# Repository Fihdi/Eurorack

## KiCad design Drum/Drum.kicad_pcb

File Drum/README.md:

Simple Kick-Drum module with triangle core VCO with variable waveshape (morphs between triangle and square wave), VCA and Envelope Generator. The envelope has CV control over the accent (maximum peak of the envelope) and decay.

The VCA is a discrete differential amplifier with an opamp amplifier stage on the output.

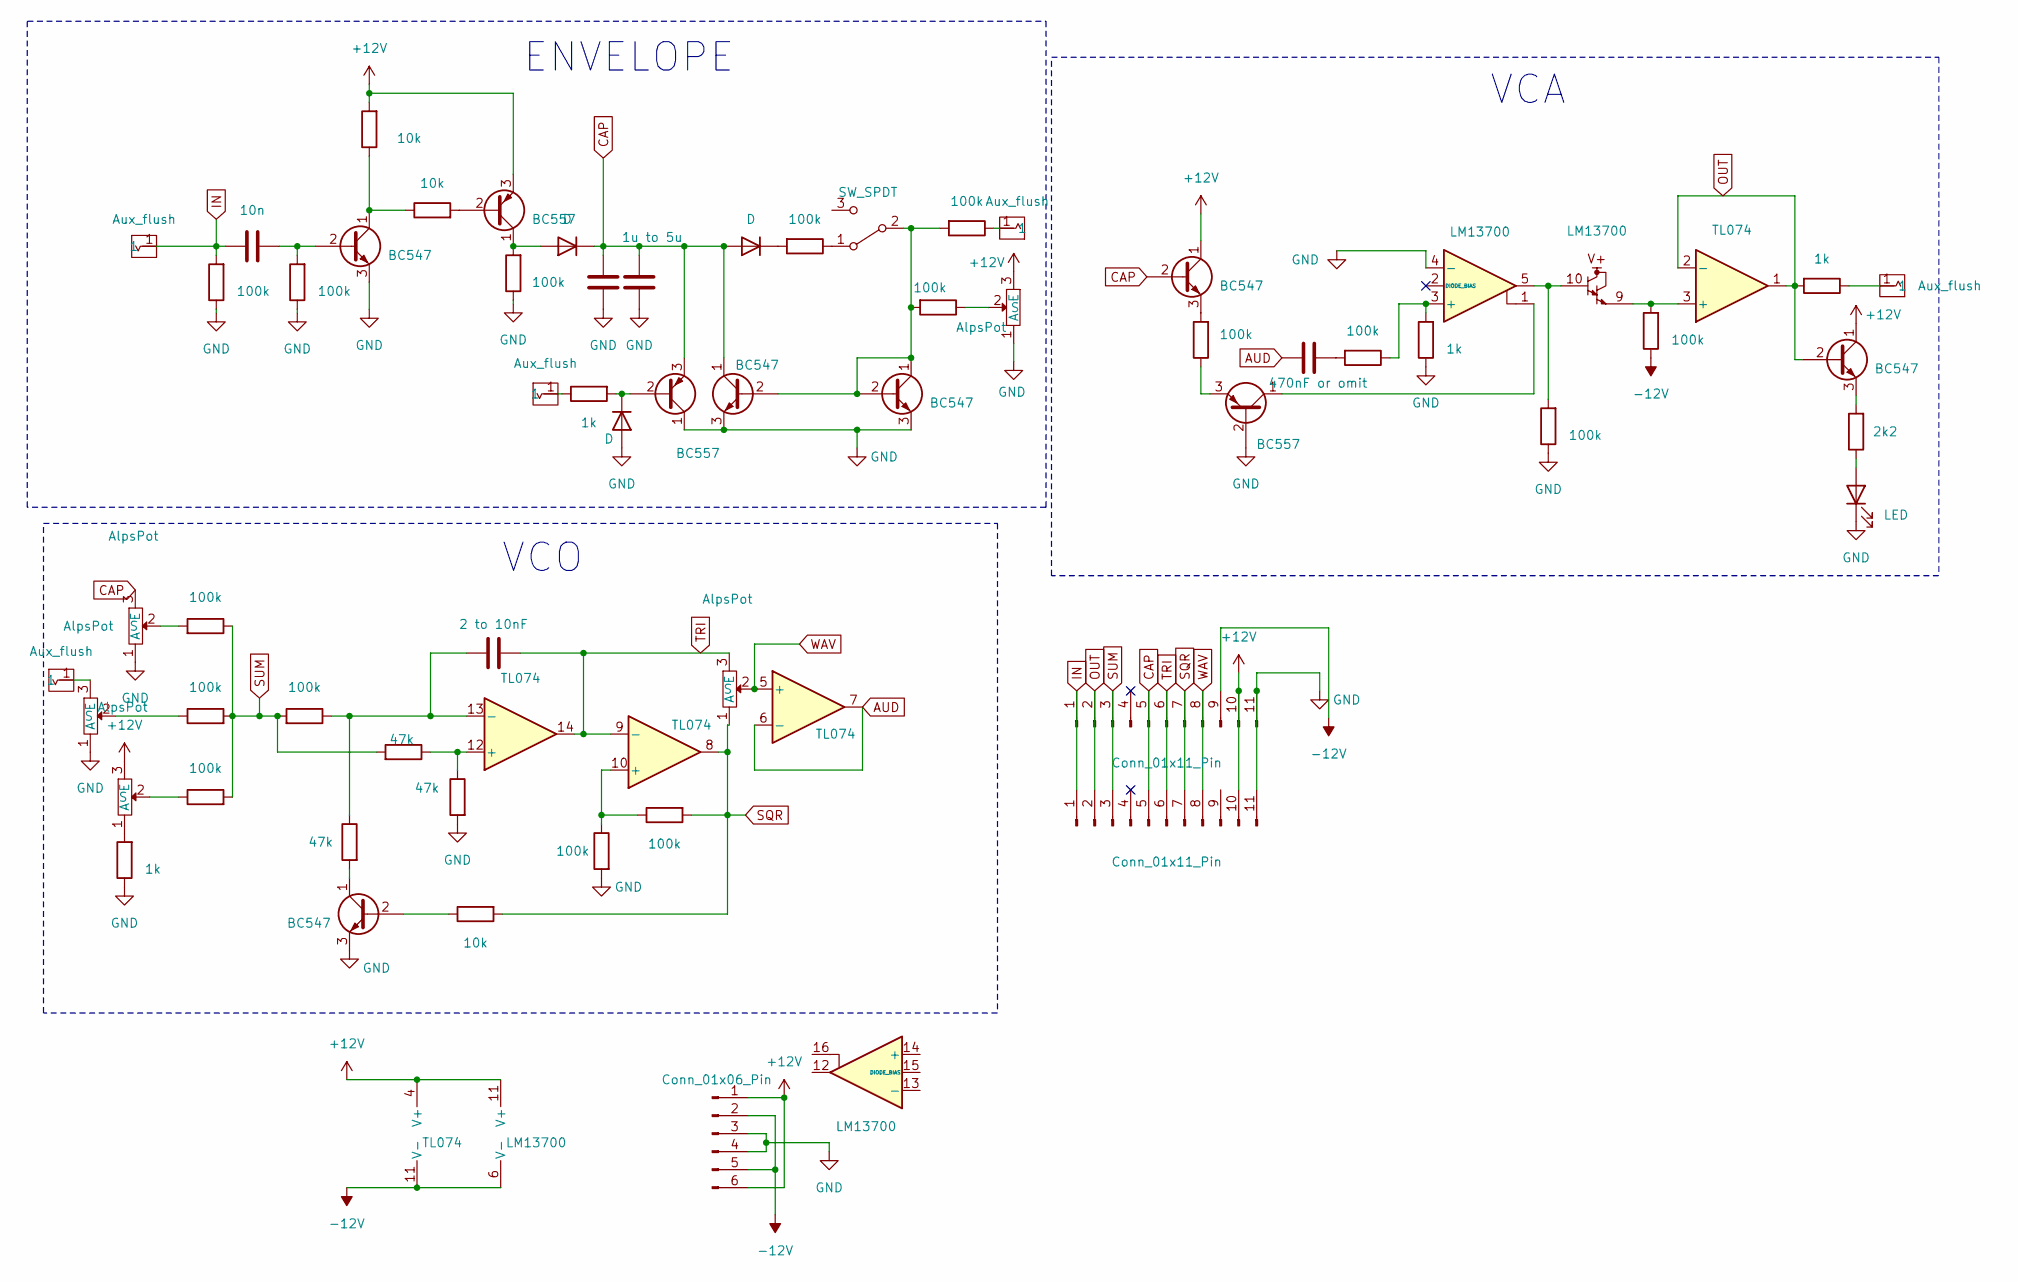
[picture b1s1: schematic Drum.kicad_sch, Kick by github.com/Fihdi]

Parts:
C1: 10n; C_Axial_L5.1mm_D3.1mm_P7.50mm_Horizontal
C2: 1u to 5u; C_Axial_L5.1mm_D3.1mm_P7.50mm_Horizontal
C3: 470nF or omit; C_Axial_L5.1mm_D3.1mm_P7.50mm_Horizontal
C4: 2 to 10nF; C_Axial_L5.1mm_D3.1mm_P7.50mm_Horizontal
C7: 5n; C_Axial_L5.1mm_D3.1mm_P7.50mm_Horizontal
D1, D3, D4: D; D_A-405_P7.62mm_Horizontal
D2: LED; LED_D5.0mm
J1: Conn_01x06_Pin; PinHeader_1x06_P2.54mm_Vertical
J2, J3: Conn_01x11_Pin; PinHeader_1x11_P2.54mm_Vertical
Q2, Q3, Q6, Q7, Q8, Q9: BC547; TO-92L_Inline_Wide
Q4, Q5, Q10: BC557; TO-92L_Inline_Wide
R1, R5, R9, R12, R13: AlpsPot
R2, R3, R4, R6, R7, R8, R10, R11, R14, R18, R19, R20, R21, R24, R29, R30: 100k; R_Axial_DIN0207_L6.3mm_D2.5mm_P7.62mm_Horizontal
R15, R28, R31: 47k; R_Axial_DIN0207_L6.3mm_D2.5mm_P7.62mm_Horizontal
R16, R25, R27, R33: 1k; R_Axial_DIN0207_L6.3mm_D2.5mm_P7.62mm_Horizontal
R17: 2k2; R_Axial_DIN0207_L6.3mm_D2.5mm_P7.62mm_Horizontal
R22, R23, R32: 10k; R_Axial_DIN0207_L6.3mm_D2.5mm_P7.62mm_Horizontal
SW1: SW_SPDT; Switch
U1, U2, U6, U7, U8: Aux_flush; 3mm5 Mono Aux
U3: TL074; DIP-14_W7.62mm
U5: LM13700; DIP-16_W7.62mm

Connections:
+12V: J1.1, J1.6, J2.10, J3.10, Q3.1 (C), Q4.3 (E), Q7.1 (C), R1.3 (E), R5.3 (E), R22.2, U3.4 (V+), U5.11 (V+)
-12V: J1.2, J1.5, J3.9, R18.1, U3.11 (V-), U5.6 (V-)
AUD: C3.1, U3.6 (-), U3.7
CAP: C2.2, C7.2, D1.1 (K), D3.2 (A), J2.5, J3.5, Q3.2 (B), Q8.1 (C), Q10.3 (E), R9.3 (E)
GND: C2.1, C7.1, D2.1 (K), D4.2 (A), J1.3, J1.4, J2.11, J3.11, Q2.3 (E), Q5.2 (B), Q6.3 (E), Q8.3 (E), Q9.3 (E), Q10.1 (C), R2.1, R4.1, R5.1 (A), R6.1, R8.1, R9.1 (A), R13.1 (A), R16.1, R25.1, R28.2, R30.2, U5.4 (-)
IN: C1.1, J2.1, J3.1, R8.2, U2.1
unnamed: C3.2, R7.2
unnamed: D1.2 (A), Q4.1 (C), R6.2
unnamed: D2.2 (A), R17.1
unnamed: D3.1 (K), R20.2
unnamed: D4.1 (K), Q10.2 (B), R33.2
unnamed: C1.2, Q2.2 (B), R4.2
unnamed: Q2.1 (C), R22.1, R23.1
unnamed: Q3.3 (E), R24.2
unnamed: Q4.2 (B), R23.2
unnamed: Q5.1 (C), U5.1
unnamed: Q5.3 (E), R24.1
unnamed: Q6.2 (B), R32.1
unnamed: Q6.1 (C), R31.2
unnamed: Q7.3 (E), R17.2
unnamed: Q8.2 (B), Q9.1 (C), Q9.2 (B), R10.2, R19.2, SW1.2 (B)
unnamed: R1.1 (A), R16.2
unnamed: R1.2 (S), R3.1
unnamed: R2.2, U5.5, U5.10
unnamed: R5.2 (S), R10.1
unnamed: R9.2 (S), R21.2
unnamed: R13.3 (E), U1.1
unnamed: R13.2 (S), R14.1
unnamed: R19.1, U8.1
unnamed: R27.1, U6.1
unnamed: R33.1, U7.1
unnamed: R20.1, SW1.1 (A)
unnamed: R18.2, U3.3 (+), U5.9
unnamed: R29.1, R30.1, U3.10 (+)
unnamed: R15.1, R28.1, U3.12 (+)
unnamed: C4.2, R11.1, R31.1, U3.13 (-)
unnamed: R7.1, R25.2, U5.3 (+)
OUT: J2.2, J3.2, Q7.2 (B), R27.2, U3.1, U3.2 (-)
SQR: J2.7, J3.7, R12.1 (A), R29.2, R32.2, U3.8
SUM: J2.3, J3.3, R3.2, R11.2, R14.2, R15.2, R21.1
TRI: C4.1, J2.6, J3.6, R12.3 (E), U3.9 (-), U3.14
WAV: J2.8, J3.8, R12.2 (S), U3.5 (+)

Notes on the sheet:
VCA
ENVELOPE
VCO

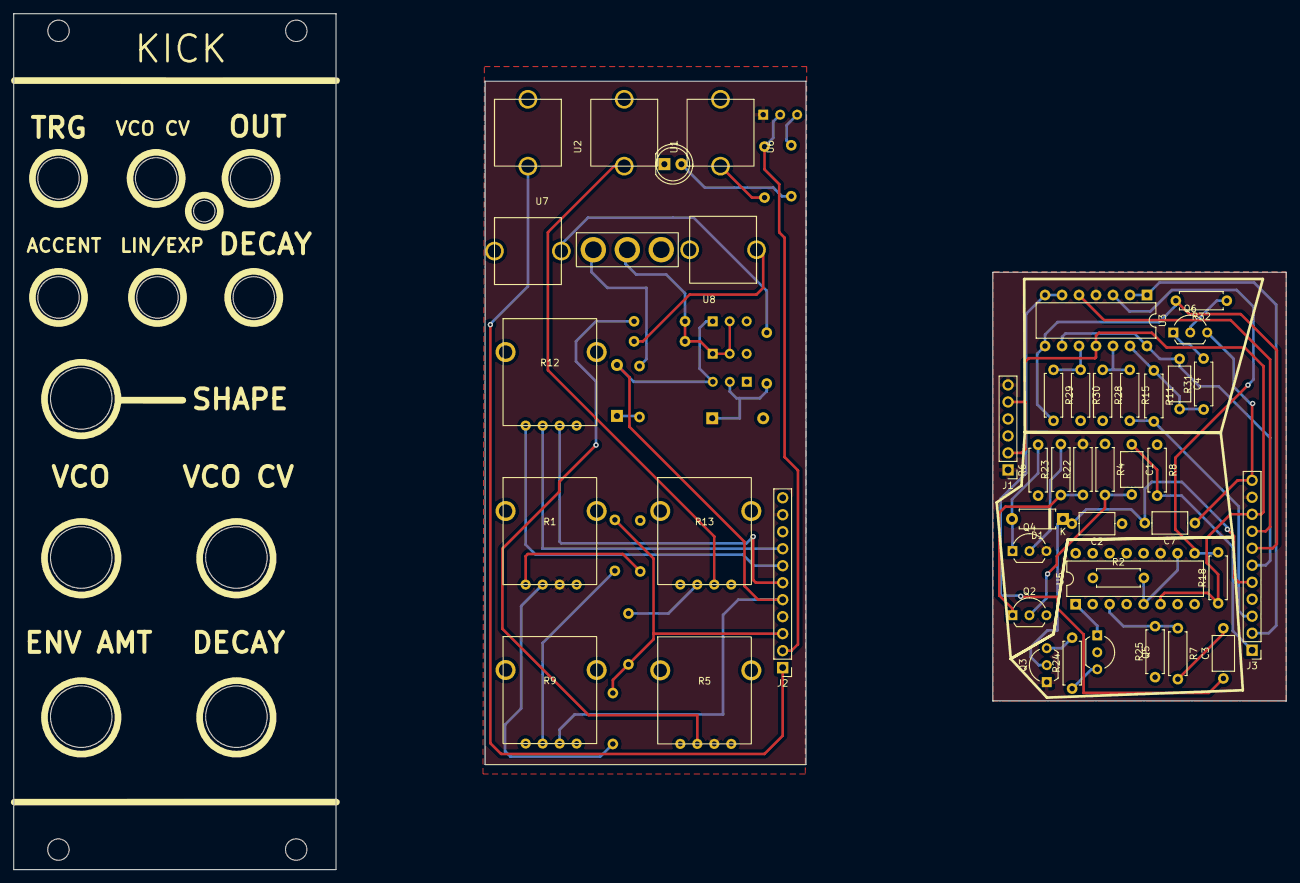
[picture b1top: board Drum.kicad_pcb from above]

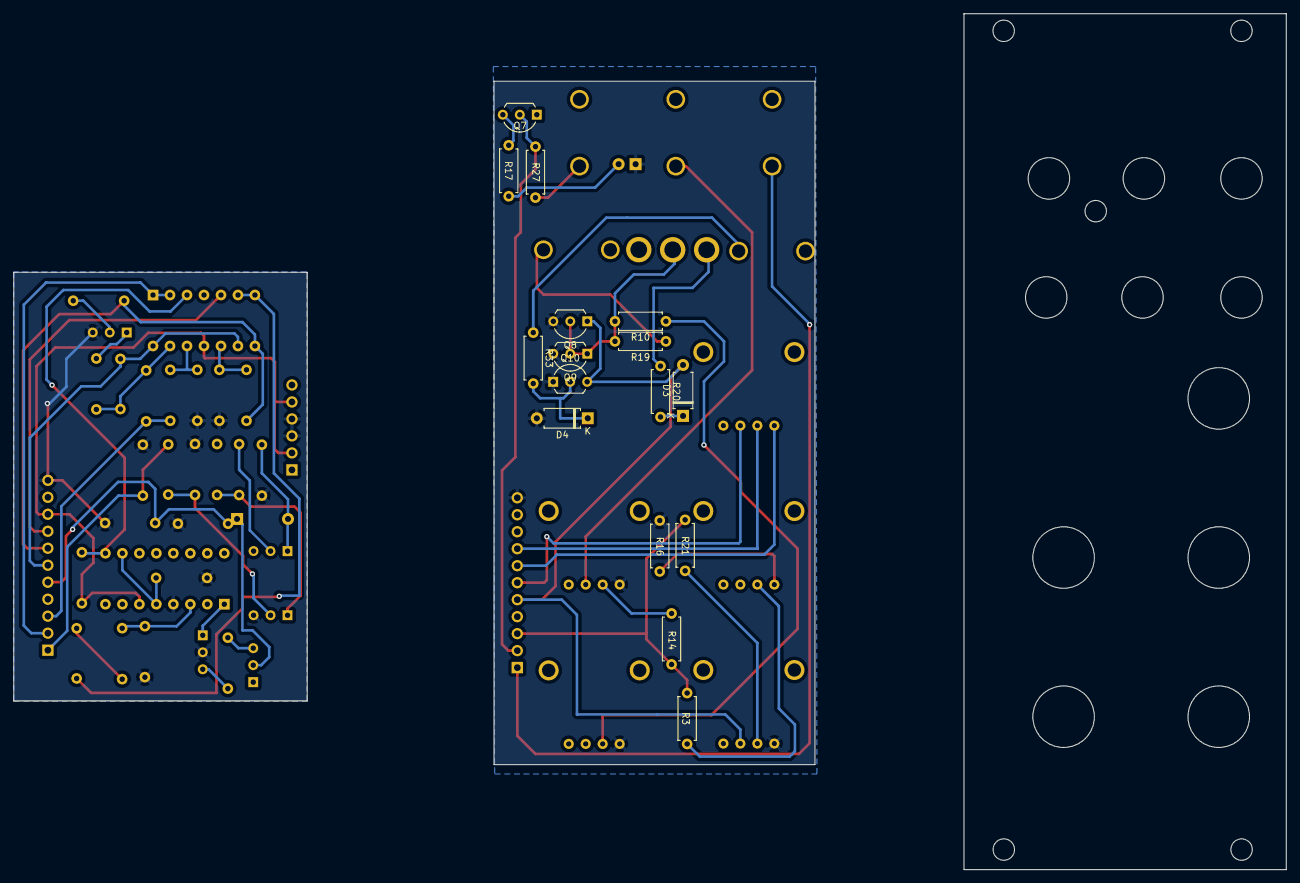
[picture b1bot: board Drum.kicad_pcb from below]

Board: 2 copper layers, 190.3 x 128.0 mm, 61 parts (16 on the bottom side), 42 nets.

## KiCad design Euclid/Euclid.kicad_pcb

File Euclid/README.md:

2 Channel Euclidean Rhythm Generator.

Has an internal clock generator which can be used as a master clock. This clock will be overwritten if an external signal on CLK IN is detected. If no signal is detected at CLK IN, the internal clock is used again. 

Channel parameters such as length and steps can be changed via pots and shifted via the SHIFT input.

A rising edge at RESET resets the channels assignments.

Upload the file "Bernoulli-Gates.ino" to repurpose the module as a "coin toss" module similar to Mutable Instruments Branches. Send a Gate or Trigger into the CLK IN input and the signal will be routed to either OUT1 or OUT2 depending on a probability. The probability is set by the rate knob.

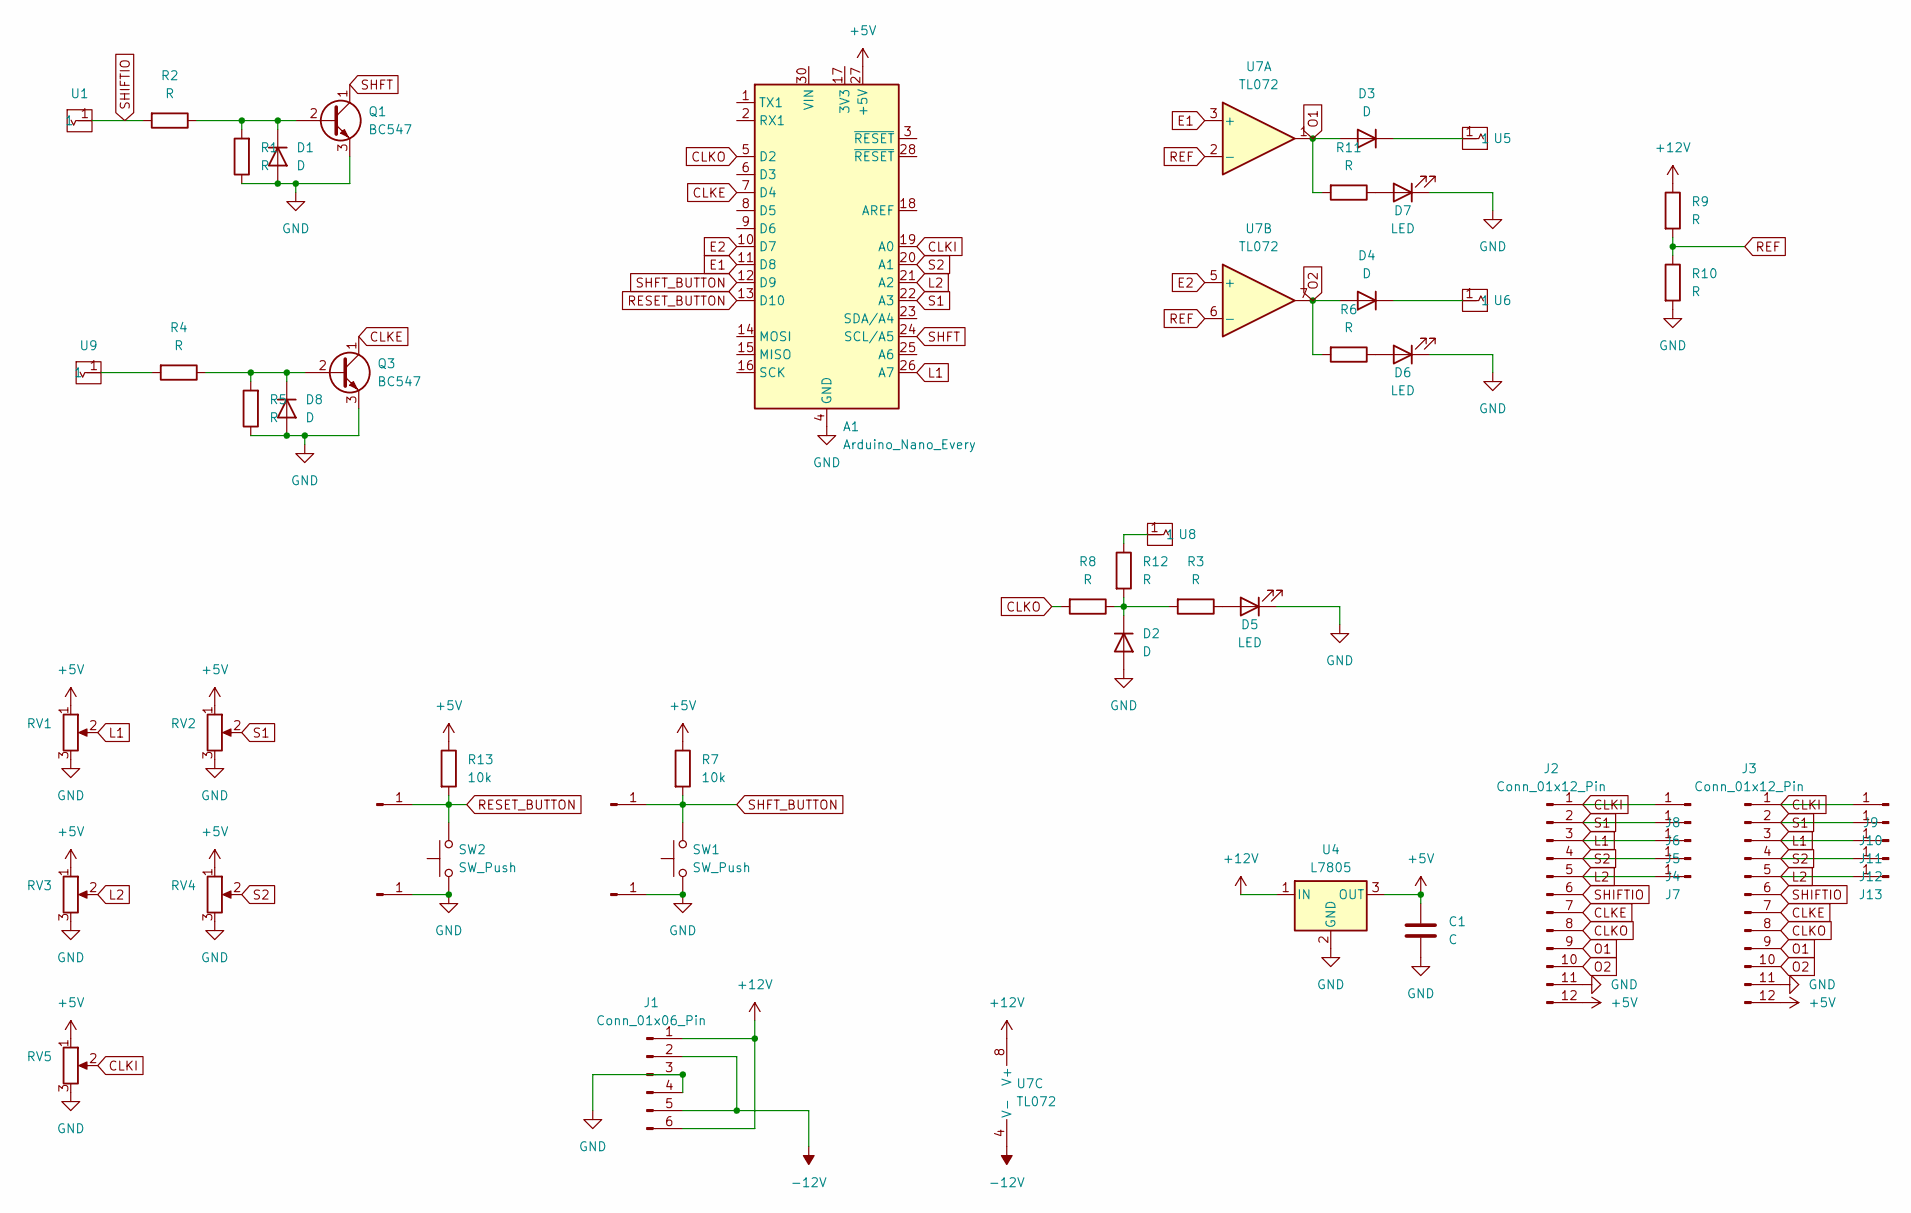
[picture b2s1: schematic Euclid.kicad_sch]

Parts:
A1: Arduino_Nano_Every; Arduino_Nano
C1: C; C_Rect_L10.3mm_W4.5mm_P7.50mm_MKS4
D1, D2, D3, D4, D8: D; D_A-405_P7.62mm_Horizontal
D5, D6, D7: LED; LED_D3.0mm
J1: Conn_01x06_Pin; PinSocket_1x06_P2.54mm_Vertical
J2, J3: Conn_01x12_Pin; PinSocket_1x12_P2.54mm_Vertical
J4, J5, J6, J7, J8, J9, J10, J11, J12, J13, J14, J15, J16, J17: Conn_01x01_Pin; PinSocket_1x01_P2.54mm_Vertical
Q1, Q3: BC547; TO-92_Inline_Wide
R1, R2, R3, R4, R5, R6, R8, R9, R10, R11, R12: R; R_Axial_DIN0207_L6.3mm_D2.5mm_P7.62mm_Horizontal
R7, R13: 10k; R_Axial_DIN0207_L6.3mm_D2.5mm_P7.62mm_Horizontal
RV1, RV2, RV3, RV4, RV5: R_Potentiometer; AlpsPot
SW1, SW2: SW_Push
U1, U5, U6, U8, U9: Aux_flush; 3mm5 Mono Aux
U4: L7805; TO-252-3_TabPin2
U7: TL072; DIP-8_W7.62mm

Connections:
+5V: A1.27 (+5V), C1.1, J2.12, J3.12, R7.1, R13.1, RV1.1, RV2.1, RV3.1, RV4.1, RV5.1, U4.3 (OUT)
+12V: J1.1, J1.6, R9.1, U4.1 (IN), U7.8 (V+)
-12V: J1.2, J1.5, U7.4 (V-)
CLKE: A1.7 (D4), J2.7, J3.7, Q3.1 (C)
CLKI: A1.19 (A0), J2.1, J3.1, J8.1, J9.1, RV5.2
CLKO: A1.5 (D2), J2.8, J3.8, R8.2
E1: A1.11 (D8), U7.3 (+)
E2: A1.10 (D7), U7.5 (+)
GND: A1.4 (GND), A1.29 (GND), C1.2, D1.2 (A), D2.2 (A), D5.1 (K), D6.1 (K), D7.1 (K), D8.2 (A), J1.3, J1.4, J2.11, J3.11, J15.1, J17.1, Q1.3 (E), Q3.3 (E), R1.1, R5.1, R10.2, RV1.3, RV2.3, RV3.3, RV4.3, RV5.3, SW1.1, SW2.1, U4.2 (GND)
L1: A1.26 (A7), J2.3, J3.3, J5.1, J11.1, RV1.2
L2: A1.21 (A2), J2.5, J3.5, J7.1, J13.1, RV3.2
unnamed: D1.1 (K), Q1.2 (B), R1.2, R2.1
unnamed: D2.1 (K), R3.2, R8.1, R12.2
unnamed: D3.1 (K), U5.1
unnamed: D4.1 (K), U6.1
unnamed: D5.2 (A), R3.1
unnamed: D6.2 (A), R6.1
unnamed: D7.2 (A), R11.1
unnamed: D8.1 (K), Q3.2 (B), R4.1, R5.2
unnamed: R4.2, U9.1
unnamed: R12.1, U8.1
O1: D3.2 (A), J2.9, J3.9, R11.2, U7.1
O2: D4.2 (A), J2.10, J3.10, R6.2, U7.7
REF: R9.2, R10.1, U7.2 (-), U7.6 (-)
RESET_BUTTON: A1.13 (D10), J16.1, R13.2, SW2.2
S1: A1.22 (A3), J2.2, J3.2, J6.1, J10.1, RV2.2
S2: A1.20 (A1), J2.4, J3.4, J4.1, J12.1, RV4.2
SHFT: A1.24 (SCL/A5), Q1.1 (C)
SHFT_BUTTON: A1.12 (D9), J14.1, R7.2, SW1.2
SHIFTIO: J2.6, J3.6, R2.2, U1.1

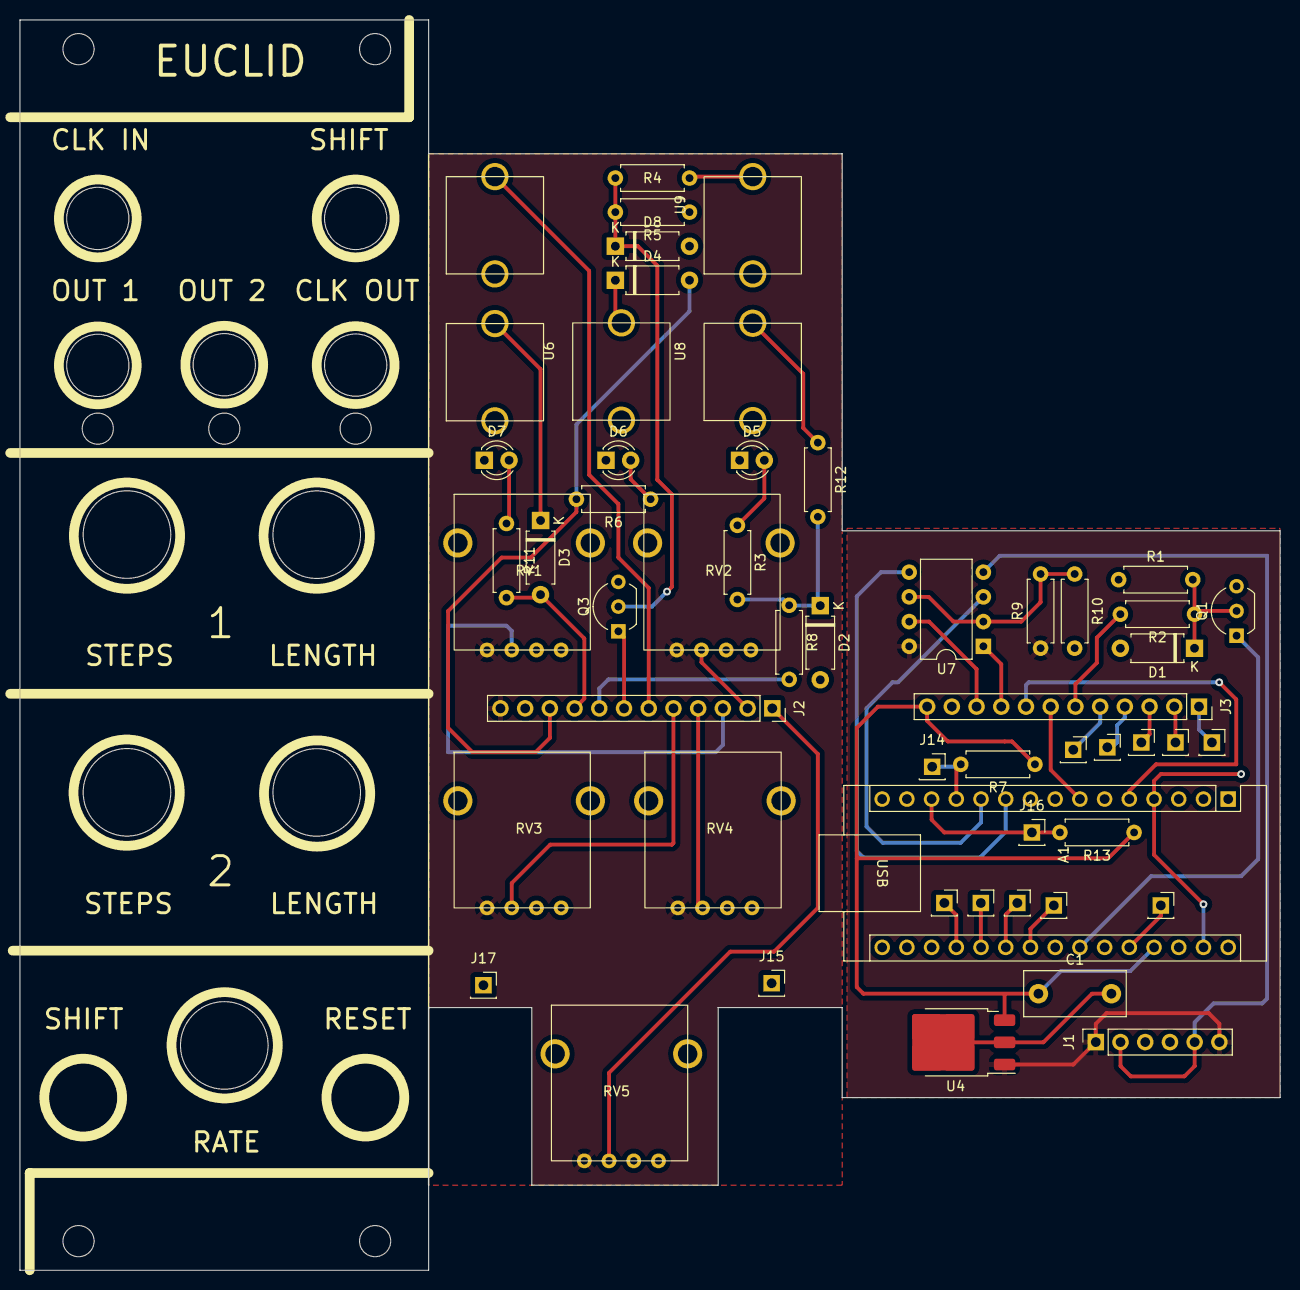
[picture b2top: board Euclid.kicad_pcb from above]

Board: 2 copper layers, 129.5 x 128.5 mm, 54 parts (0 on the bottom side), 30 nets.

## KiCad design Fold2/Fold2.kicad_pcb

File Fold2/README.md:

# A wavefolder with CV control over the amount of folds.

Me and [Davey Graham](https://github.com/DaveyGraham/Daveys_Deadband) were working on wavefolders at the same time independently. A few days after I posted this schematic for a simple wavefolder, Davey has extended upon it:

CAP is the input signal being clamped at +CV and -CV. I then subtract the original signal from the clamped signal to get a folded output.

Extending the clamping circuit with multiple limits and using the same principle as in Buchlas "Timbre Modulation" circuit where the input signal is split into multiple "deadbands" and then re-added and subtracted from each other to produce the folded output, we get the full circuit that was made by Davey Graham. 

The deadbands are made using this diode structure, it can also be seen as a clamping circuit with variable clamping voltages:

An example with the upper limit being 5V and the lower limit being 3V. The output of this circuit follows the input signal as long as it is within the upper and lower limits. The output never exceeds these limits (ignoring the diode drop).

The resistor chain and buffers are there to provide the upper and lower limits for the diodes.

# How to get a folded output from deadbands?

As in the Buchla circuit, every other band is summed together, resulting in two signals A and B (I did not draw the summing stages for simplicity) 
With no input, the bias voltages between the diodes sum up to zero volts, so with 0V in you get 0V out. OK. Boring.

With a sine input the signals A and B cross each other, and when B is subtracted from A, the resulting wave changes in polarity at every crossing, and we get folding. 

# How to add voltage control?

To get a fold, the input voltage needs to cross either the upper or lower limit of the clamping circuit, so the amount of folds depends on the amplitude and how many limits it is crossing. Using a VCA with a high gain gives control over the amplitude and thus the amount of folds. The output of the VCA is also directly fed to the "VCA" output, since you can never have enough VCAs.

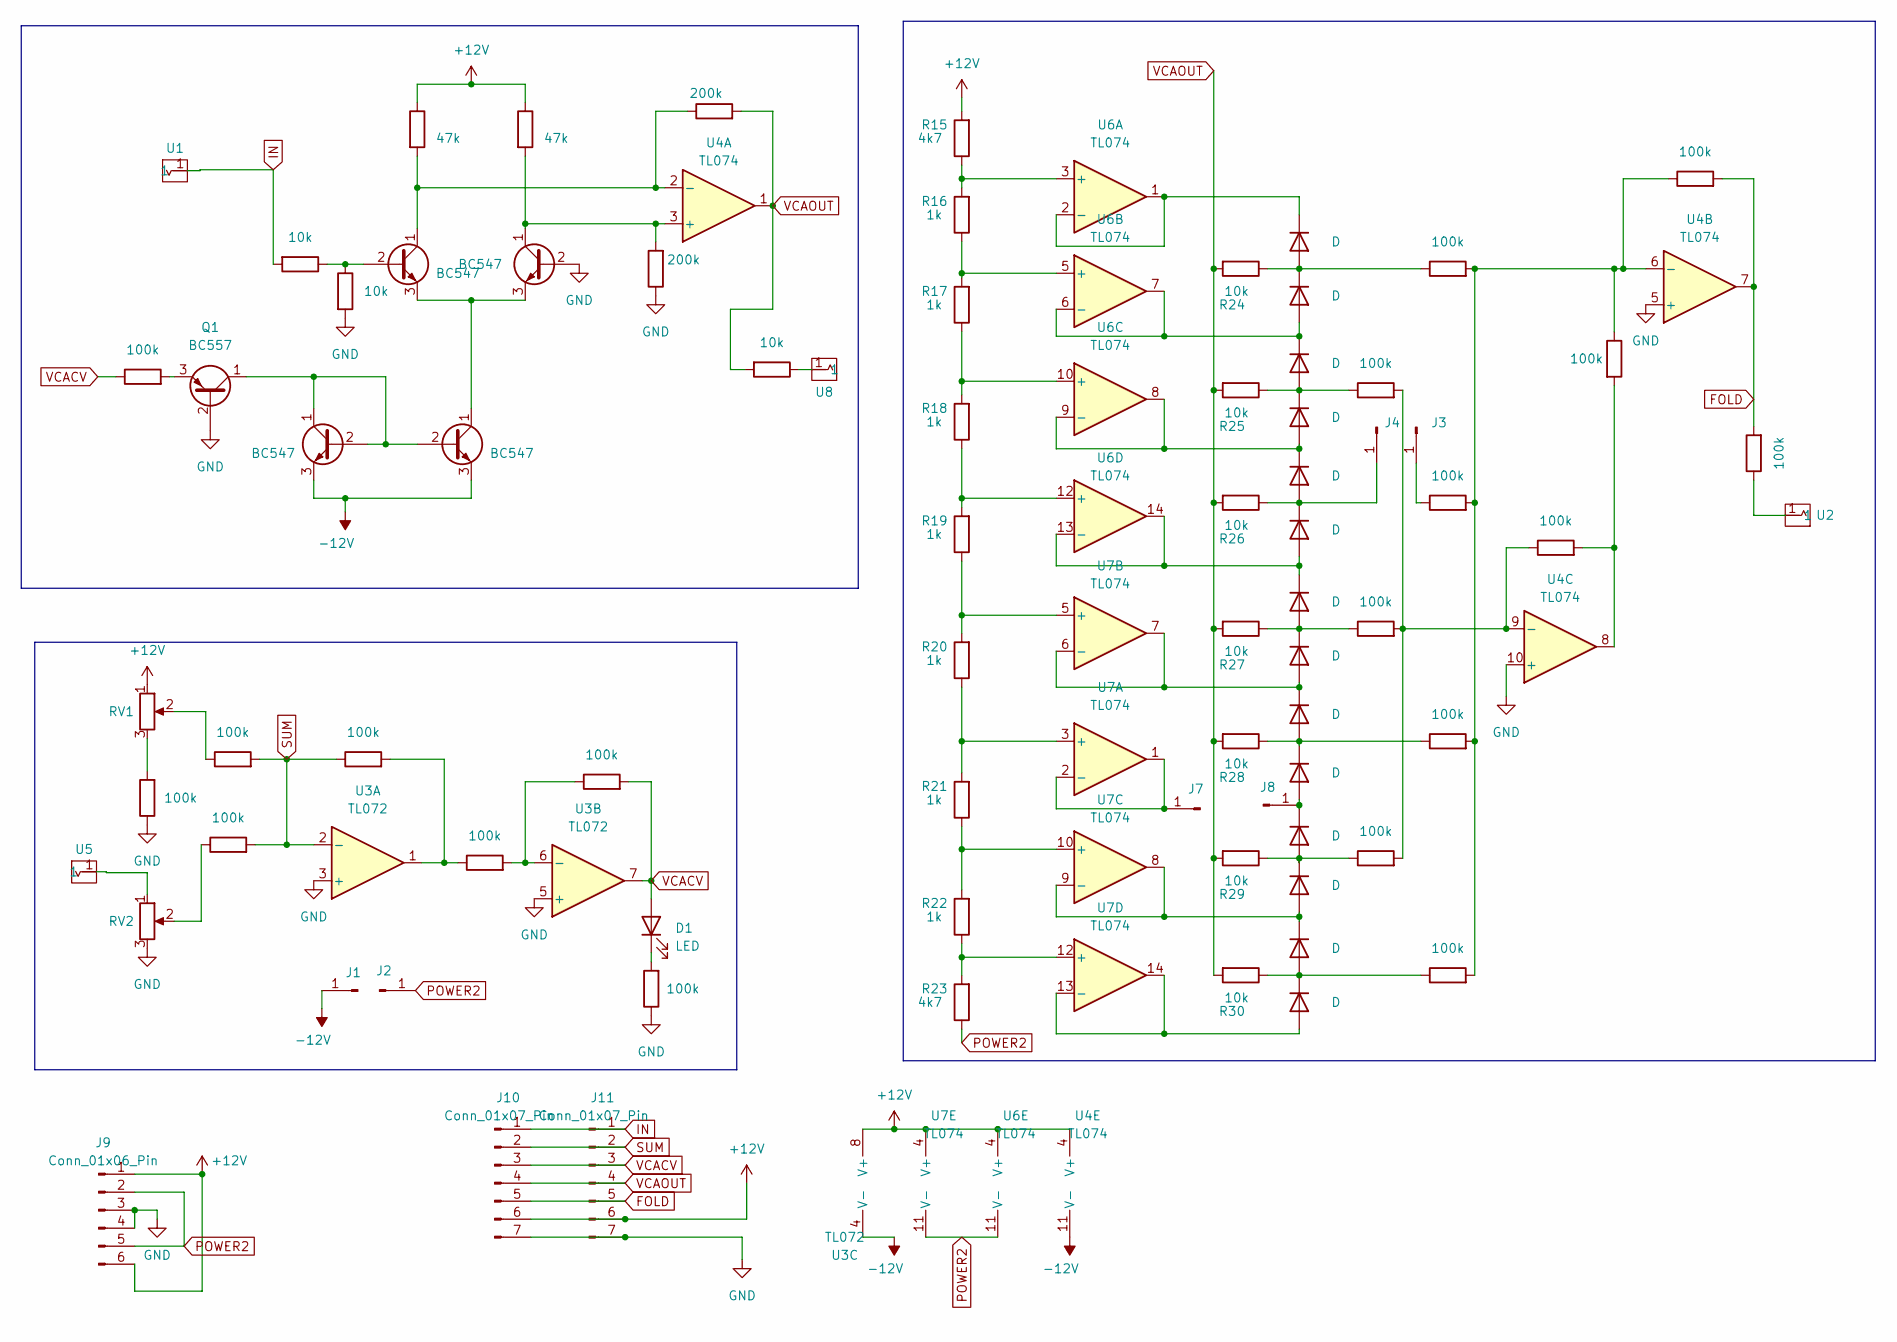
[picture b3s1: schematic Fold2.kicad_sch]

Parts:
D1: LED; LED_D3.0mm
D2, D3, D4, D5, D6, D7, D8, D9, D10, D11, D12, D13, D14, D15: D; D_A-405_P5.08mm_Vertical_AnodeUp
J1, J2, J3, J4, J7, J8: Conn_01x01_Pin; PinSocket_1x01_P2.54mm_Vertical
J9: Conn_01x06_Pin; PinHeader_1x06_P2.54mm_Vertical
J10, J11: Conn_01x07_Pin; PinSocket_1x07_P2.54mm_Vertical
Q1: BC557; TO-92L_Inline_Wide
Q2, Q3, Q4, Q5: BC547; TO-92_Inline_Wide
R1, R2, R3, R6, R8, R10, R11, R14, R31, R32, R33, R34, R35, R36, R37, R38, R39, R40, R42: 100k; R_Axial_DIN0204_L3.6mm_D1.6mm_P7.62mm_Horizontal
R4, R5, R24, R25, R26, R27, R28, R29, R30, R41: 10k; R_Axial_DIN0204_L3.6mm_D1.6mm_P7.62mm_Horizontal
R7, R9: 47k; R_Axial_DIN0204_L3.6mm_D1.6mm_P7.62mm_Horizontal
R12, R13: 200k; R_Axial_DIN0204_L3.6mm_D1.6mm_P7.62mm_Horizontal
R15, R23: 4k7; R_Axial_DIN0204_L3.6mm_D1.6mm_P7.62mm_Horizontal
R16, R17, R18, R19, R20, R21, R22: 1k; R_Axial_DIN0204_L3.6mm_D1.6mm_P7.62mm_Horizontal
RV1, RV2: R_Potentiometer; AlpsPot
U1, U2, U5, U8: Aux_flush; 3mm5 Mono Aux
U3: TL072; DIP-8_W7.62mm
U4, U6, U7: TL074; DIP-14_W7.62mm

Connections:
+12V: J9.1, J9.6, J10.6, J11.6, R7.1, R9.1, R15.2, RV1.1, U3.8 (V+), U4.4 (V+), U6.4 (V+), U7.4 (V+)
-12V: J1.1, Q2.3 (E), Q4.3 (E), U3.4 (V-), U4.11 (V-)
FOLD: J10.5, J11.5, R14.2, R40.2, U4.7
GND: J9.3, J9.4, J10.7, J11.7, Q1.2 (B), Q5.2 (B), R5.2, R11.1, R12.1, R42.1, RV2.3, U3.3 (+), U3.5 (+), U4.5 (+), U4.10 (+)
IN: J10.1, J11.1, R4.2, U1.1
unnamed: D1.1 (K), R11.2
unnamed: D2.2 (A), D3.1 (K), R24.1, R34.1
unnamed: D2.1 (K), U6.1, U6.2 (-)
unnamed: D3.2 (A), D4.1 (K), U6.6 (-), U6.7
unnamed: D4.2 (A), D5.1 (K), R25.1, R31.1
unnamed: D5.2 (A), D6.1 (K), U6.8, U6.9 (-)
unnamed: D6.2 (A), D7.1 (K), J4.1, R26.1
unnamed: D7.2 (A), D8.1 (K), U6.13 (-), U6.14
unnamed: D8.2 (A), D9.1 (K), R27.1, R32.1
unnamed: D10.2 (A), D11.1 (K), R28.1, R36.1
unnamed: D9.2 (A), D10.1 (K), U7.6 (-), U7.7
unnamed: D11.2 (A), D12.1 (K), J8.1
unnamed: D12.2 (A), D13.1 (K), R29.1, R33.1
unnamed: D13.2 (A), D14.1 (K), U7.8, U7.9 (-)
unnamed: D14.2 (A), D15.1 (K), R30.1, R37.1
unnamed: D15.2 (A), U7.13 (-), U7.14
unnamed: J3.1, R35.1
unnamed: J7.1, U7.1, U7.2 (-)
unnamed: Q1.1 (C), Q2.1 (C), Q2.2 (B), Q4.2 (B)
unnamed: Q1.3 (E), R1.2
unnamed: Q3.2 (B), R4.1, R5.1
unnamed: Q3.1 (C), R7.2, R13.1, U4.2 (-)
unnamed: Q3.3 (E), Q4.1 (C), Q5.3 (E)
unnamed: Q5.1 (C), R9.2, R12.2, U4.3 (+)
unnamed: R2.1, RV1.2
unnamed: R3.1, RV2.2
unnamed: R6.2, R8.1, U3.1
unnamed: R14.1, U2.1
unnamed: R38.2, R39.2, U4.8
unnamed: R41.1, U8.1
unnamed: R42.2, RV1.3
unnamed: RV2.1, U5.1
unnamed: R8.2, R10.1, U3.6 (-)
unnamed: R34.2, R35.2, R36.2, R37.2, R39.1, R40.1, U4.6 (-)
unnamed: R31.2, R32.2, R33.2, R38.1, U4.9 (-)
unnamed: R15.1, R16.2, U6.3 (+)
unnamed: R16.1, R17.2, U6.5 (+)
unnamed: R17.1, R18.2, U6.10 (+)
unnamed: R18.1, R19.2, U6.12 (+)
unnamed: R20.1, R21.2, U7.3 (+)
unnamed: R19.1, R20.2, U7.5 (+)
unnamed: R21.1, R22.2, U7.10 (+)
unnamed: R22.1, R23.2, U7.12 (+)
POWER2: J2.1, J9.2, J9.5, R23.1, U6.11 (V-), U7.11 (V-)
SUM: J10.2, J11.2, R2.2, R3.2, R6.1, U3.2 (-)
VCACV: D1.2 (A), J10.3, J11.3, R1.1, R10.2, U3.7
VCAOUT: J10.4, J11.4, R13.2, R24.2, R25.2, R26.2, R27.2, R28.2, R29.2, R30.2, R41.2, U4.1

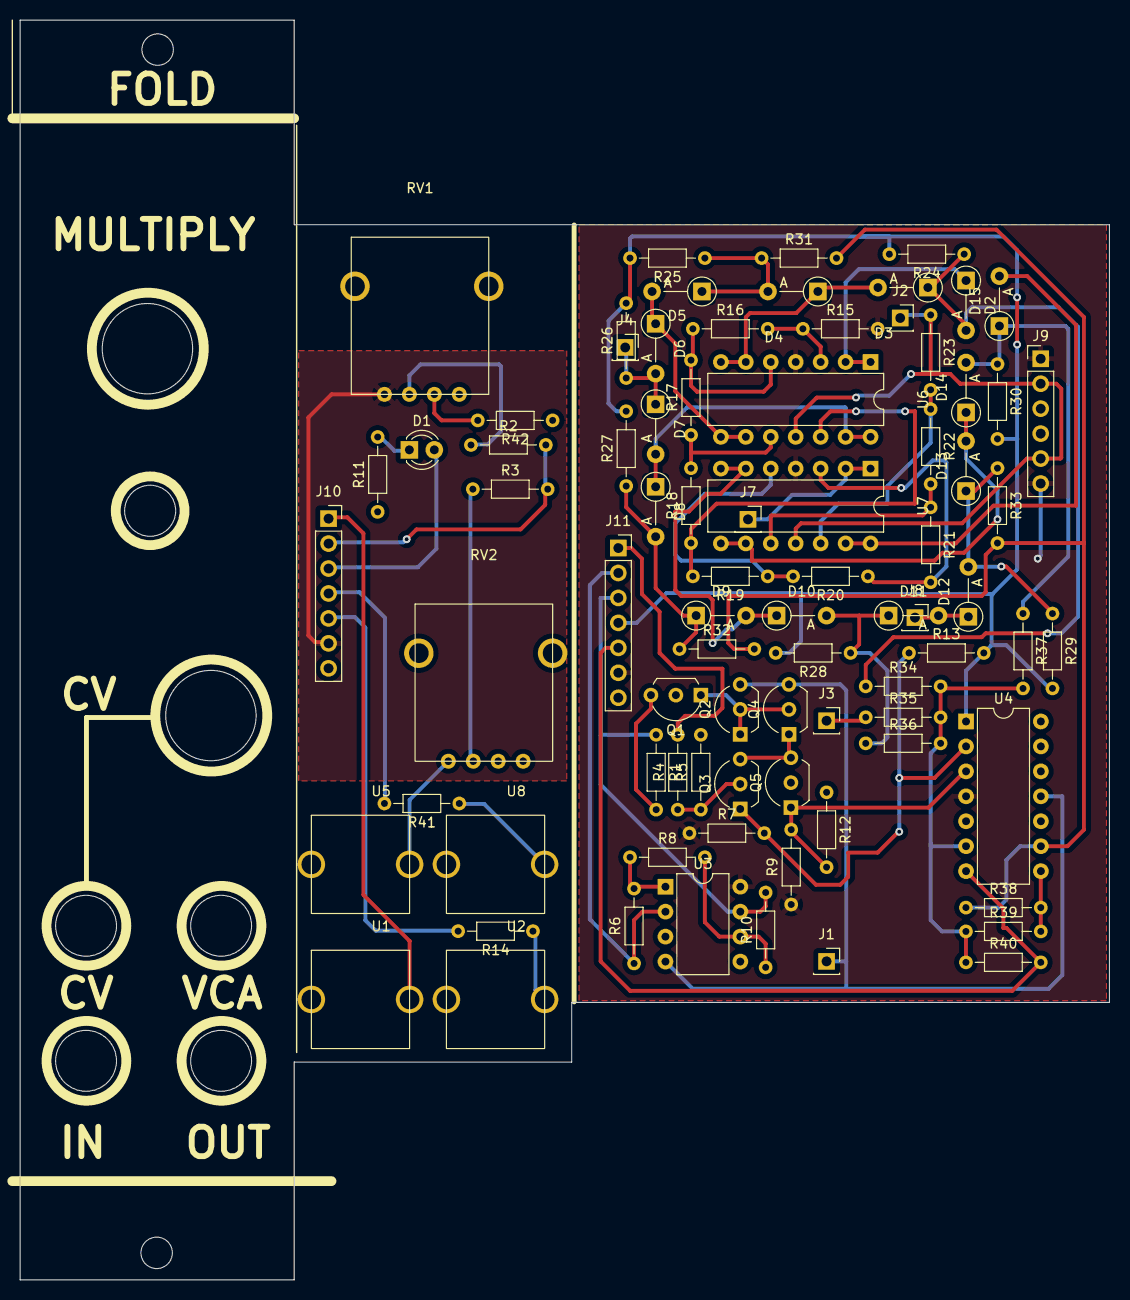
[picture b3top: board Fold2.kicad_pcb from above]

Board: 2 copper layers, 110.9 x 128.2 mm, 81 parts (0 on the bottom side), 52 nets.

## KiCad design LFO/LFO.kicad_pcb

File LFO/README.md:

No attenuator for CV. No Reset or Sync input. No inverted Square output.

MORE LEDS!

Very Basic Design, will probably come up with something of my own later.

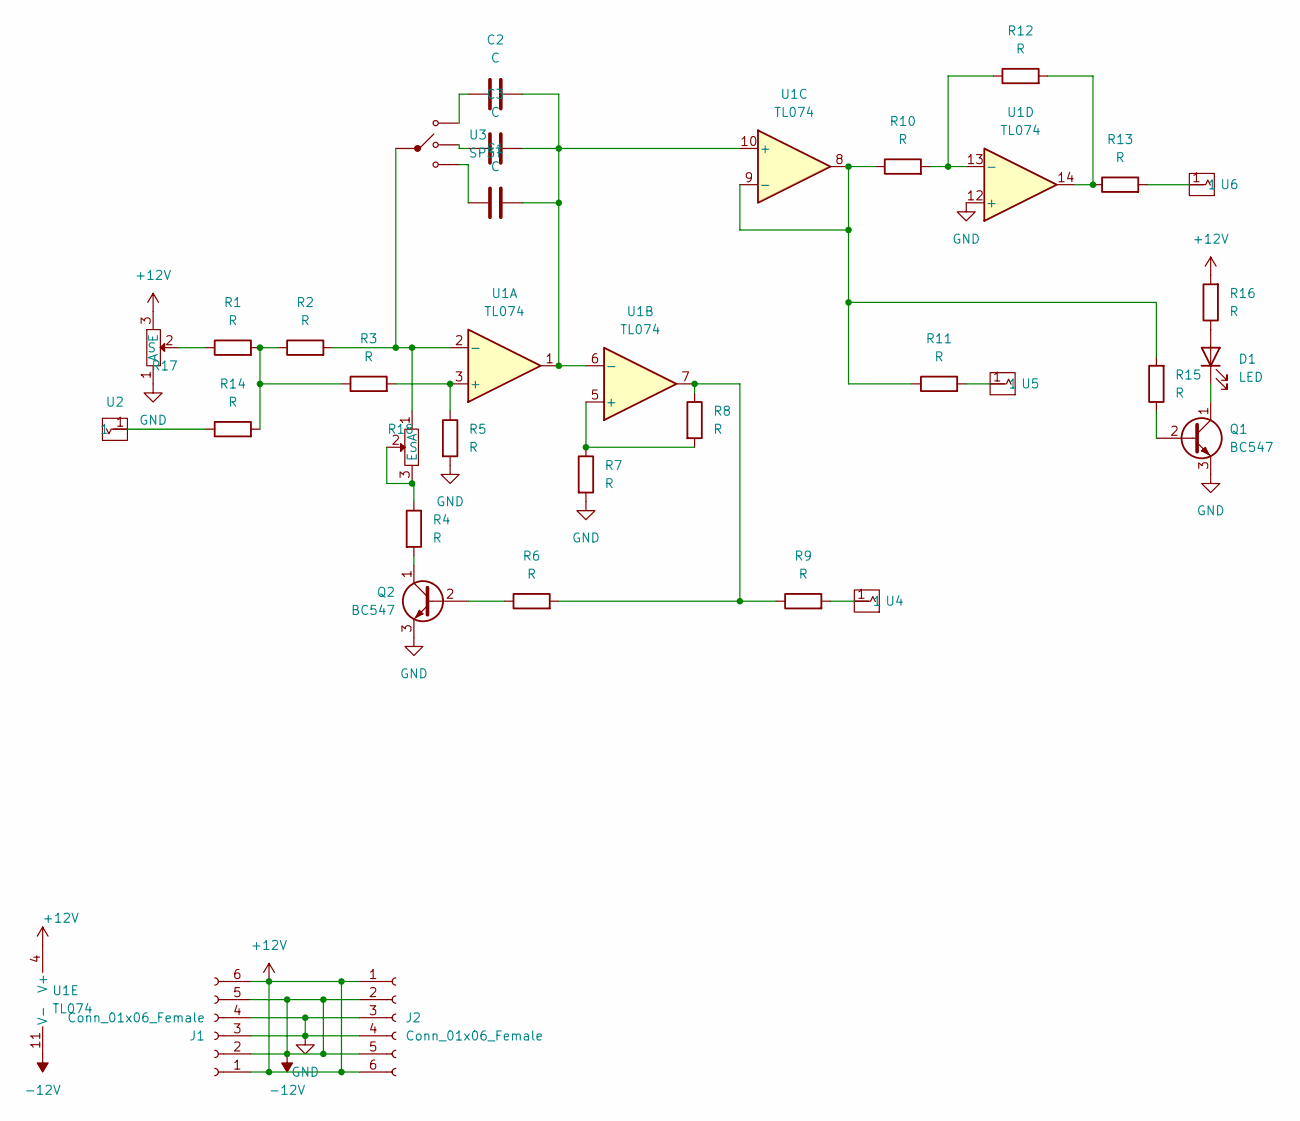
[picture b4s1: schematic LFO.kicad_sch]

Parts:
C1, C2, C3: C; C_Axial_L3.8mm_D2.6mm_P10.00mm_Horizontal
D1: LED; LED_D5.0mm
J1, J2: Conn_01x06_Female; PinHeader_1x06_P2.54mm_Vertical
Q1, Q2: BC547; TO-92L_Inline_Wide
R1, R2, R3, R4, R5, R6, R7, R8, R9, R10, R11, R12, R13, R14, R15, R16: R; R_Axial_DIN0204_L3.6mm_D1.6mm_P7.62mm_Horizontal
R17, R18: AlpsPot
U1: TL074; DIP-14_W7.62mm
U2, U4, U5, U6: Aux_flush; aux_flush
U3: SP3T

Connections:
+12V: J1.1, J1.6, J2.1, J2.6, R16.2, R17.3 (E), U1.4 (V+)
-12V: J1.2, J1.5, J2.2, J2.5, U1.11 (V-)
GND: J1.3, J1.4, J2.3, J2.4, Q1.3 (E), Q2.3 (E), R5.2, R7.2, R17.1 (A), U1.12 (+)
unnamed: C1.1, U3.4
unnamed: C1.2, C2.2, C3.2, U1.1, U1.6 (-), U1.10 (+)
unnamed: C2.1, U3.1
unnamed: C3.1, U3.3
unnamed: D1.1 (K), Q1.1 (C)
unnamed: D1.2 (A), R16.1
unnamed: Q1.2 (B), R15.1
unnamed: Q2.1 (C), R4.2
unnamed: Q2.2 (B), R6.1
unnamed: R1.1, R17.2 (S)
unnamed: R1.2, R2.1, R3.1, R14.2
unnamed: R2.2, R18.1 (A), U1.2 (-), U3.2
unnamed: R3.2, R5.1, U1.3 (+)
unnamed: R4.1, R18.2 (S), R18.3 (E)
unnamed: R6.2, R8.1, R9.1, U1.7
unnamed: R7.1, R8.2, U1.5 (+)
unnamed: R9.2, U4.1
unnamed: R10.1, R11.1, R15.2, U1.8, U1.9 (-)
unnamed: R10.2, R12.1, U1.13 (-)
unnamed: R11.2, U5.1
unnamed: R12.2, R13.1, U1.14
unnamed: R13.2, U6.1
unnamed: R14.1, U2.1

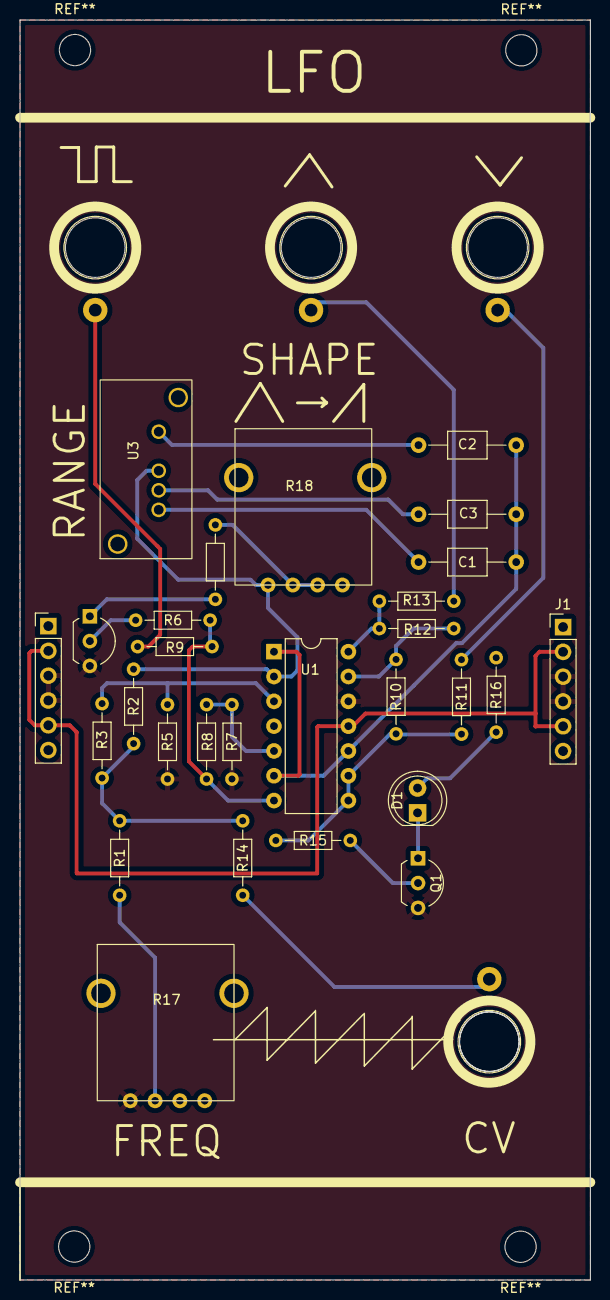
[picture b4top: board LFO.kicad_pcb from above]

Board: 2 copper layers, 58.4 x 129.0 mm, 32 parts (0 on the bottom side), 26 nets.
